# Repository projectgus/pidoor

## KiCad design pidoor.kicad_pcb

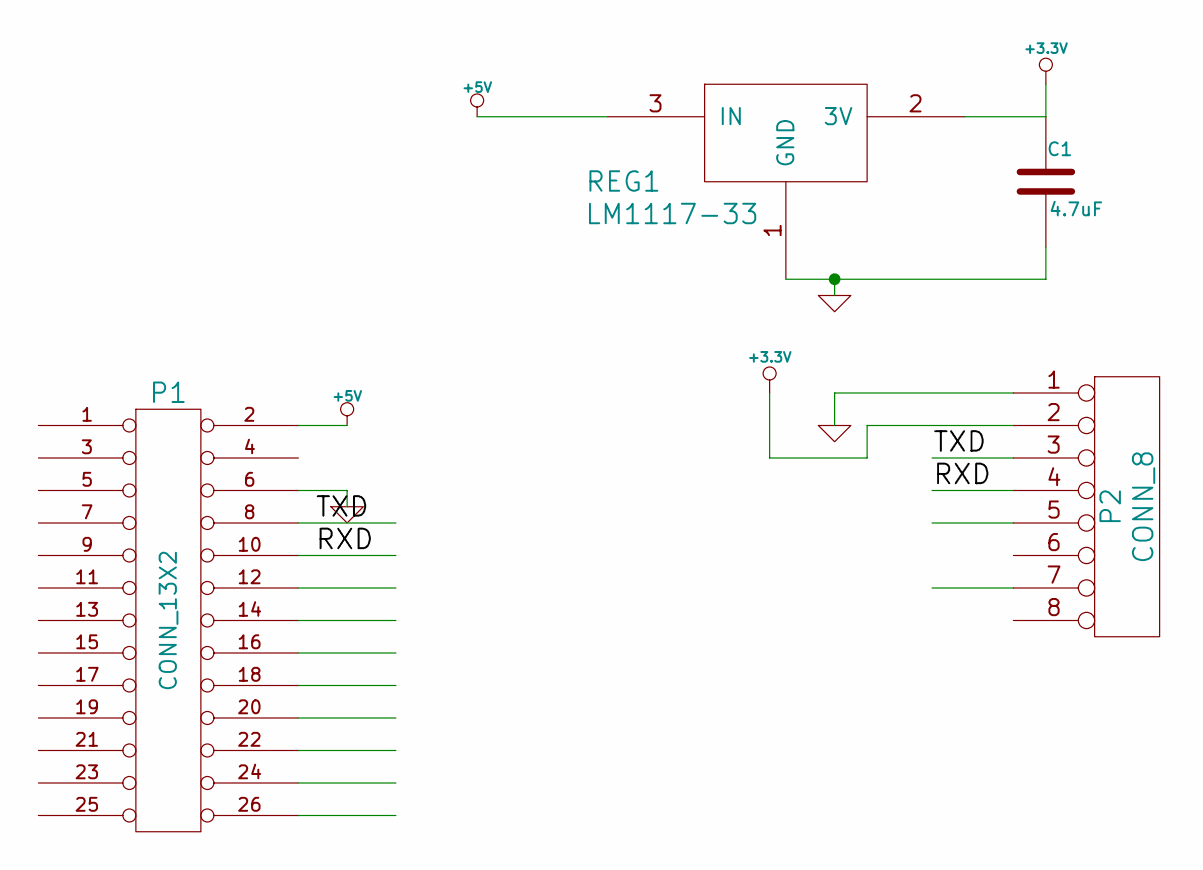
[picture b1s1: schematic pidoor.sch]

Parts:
C1: 4.7uF
P1: CONN_13X2
P2: CONN_8
REG1: LM1117-33

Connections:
+3.3V: C1.1, P2.2, REG1.2 (3V)
+5V: P1.2, REG1.3 (IN)
/RXD: P1.10, P2.4
/TXD: P1.8, P2.3
GND: C1.2, P1.6, P2.1, REG1.1 (GND)

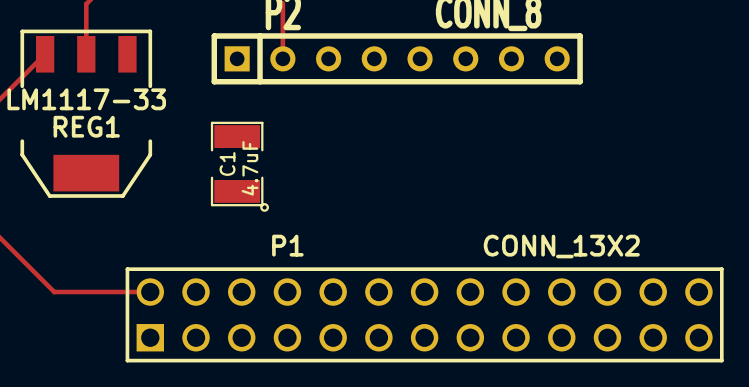
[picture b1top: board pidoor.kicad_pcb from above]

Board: 2 copper layers, 4 parts (0 on the bottom side), 5 nets.

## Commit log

2013-05-14 Getting started, work in progress from tonight's workshop
